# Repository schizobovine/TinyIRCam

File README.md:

# TinyIRCam
Simple mash up of a [TinyScreen+](https://tinycircuits.com/collections/all/products/tinyscreenplus) and a 8x8 [GridEye IR sensor breakout](https://www.tindie.com/products/onehorse/grid-eye-8-x-8-ir-array/>).

## Building
You will need the [TinyScreen+ board definition installed](https://tinycircuits.com/blogs/learn/158833543-tinyscreen-setup) in a working Arduino 1.6+ environment to build the code.

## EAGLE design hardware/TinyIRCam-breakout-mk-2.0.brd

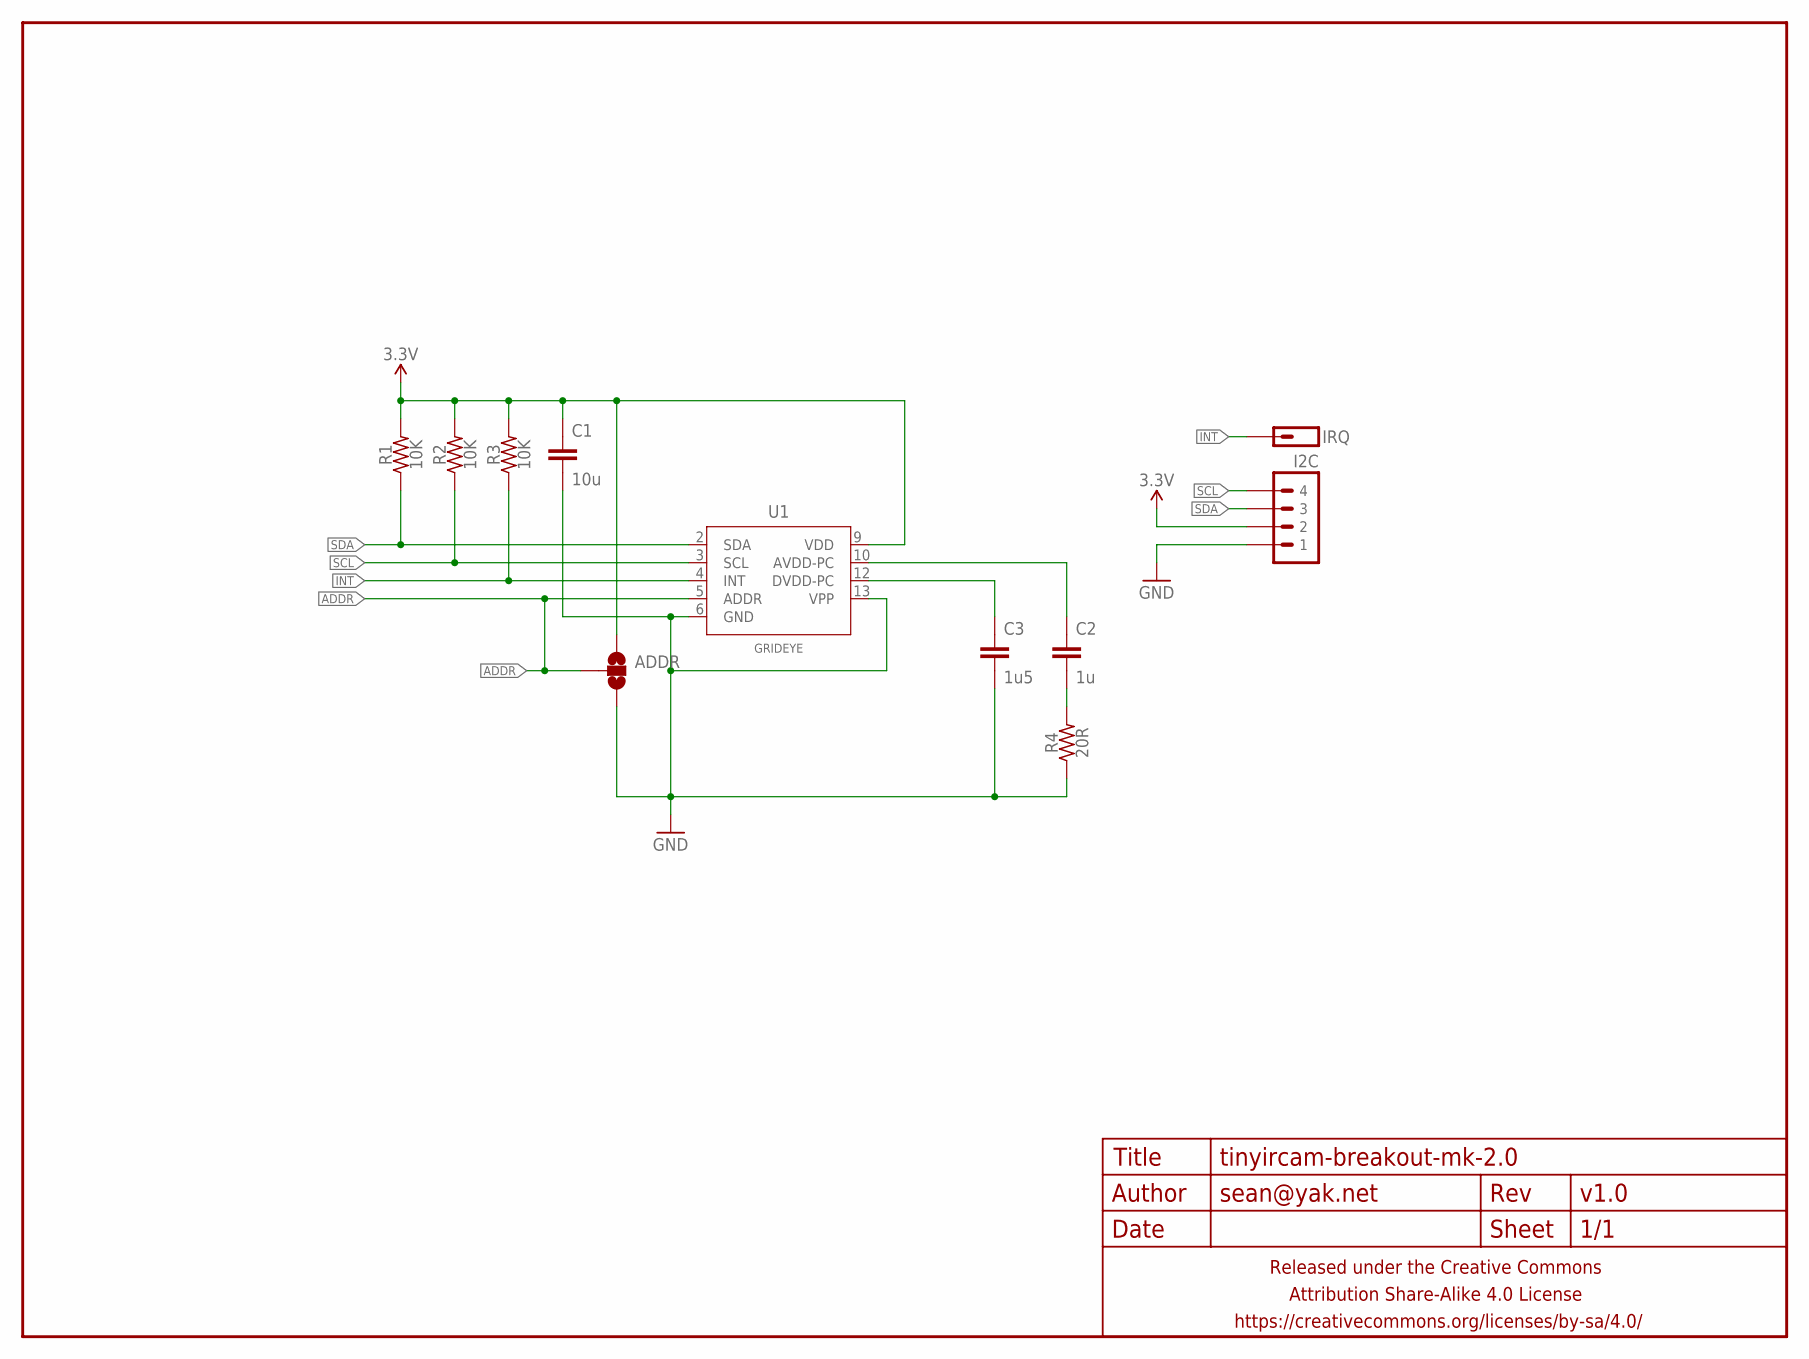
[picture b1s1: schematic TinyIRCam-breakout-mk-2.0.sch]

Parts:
ADDR: JUMPER-PAD-3-NOSMALLER; PAD-JUMPER-3-NO_YES_SILK_FULL_BOX_SMALLER
C1: 10u; C0603-TIGHTER
C2: 1u; C0603-TIGHTER
C3: 1u5; C0603-TIGHTER
FRAME1: FRAME-LETTERNO_PACKAGE; DUMMY
I2C: M04PTH-CENTERED; 1X04-PTH-VERT-CENTER
IRQ: M01PTH; 1X01
R1, R2, R3: 10K; R0603-TIGHTER
R4: 20R; R0603-TIGHTER
U1: GRIDEYE; GRIDEYE-FATTER

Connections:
3.3V: ADDR.1, C1.1, I2C.2, R1.2, R2.2, R3.2, U1.9 (VDD)
ADDR: ADDR.2, U1.5 (ADDR)
GND: ADDR.3, C1.2, C3.2, I2C.1, R4.1, U1.6 (GND), U1.13 (VPP)
INT: IRQ.1, R3.1, U1.4 (INT)
unnamed: C2.2, R4.2
unnamed: C3.1, U1.12 (DVDD-PC)
unnamed: C2.1, U1.10 (AVDD-PC)
SCL: I2C.4, R2.1, U1.3 (SCL)
SDA: I2C.3, R1.1, U1.2 (SDA)

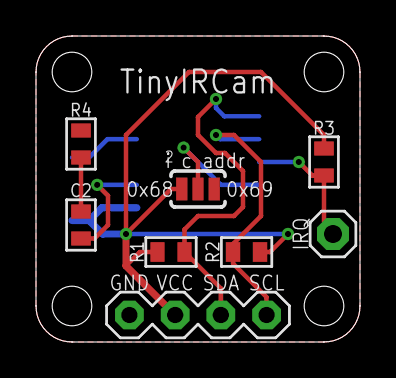
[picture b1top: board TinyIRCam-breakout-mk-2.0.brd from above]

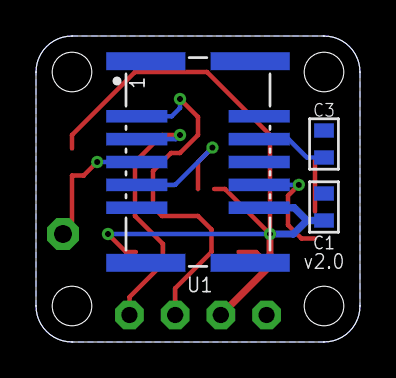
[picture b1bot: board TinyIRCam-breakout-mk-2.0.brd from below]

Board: 2 copper layers, 18.0 x 17.0 mm, 12 parts (3 on the bottom side), 9 nets.

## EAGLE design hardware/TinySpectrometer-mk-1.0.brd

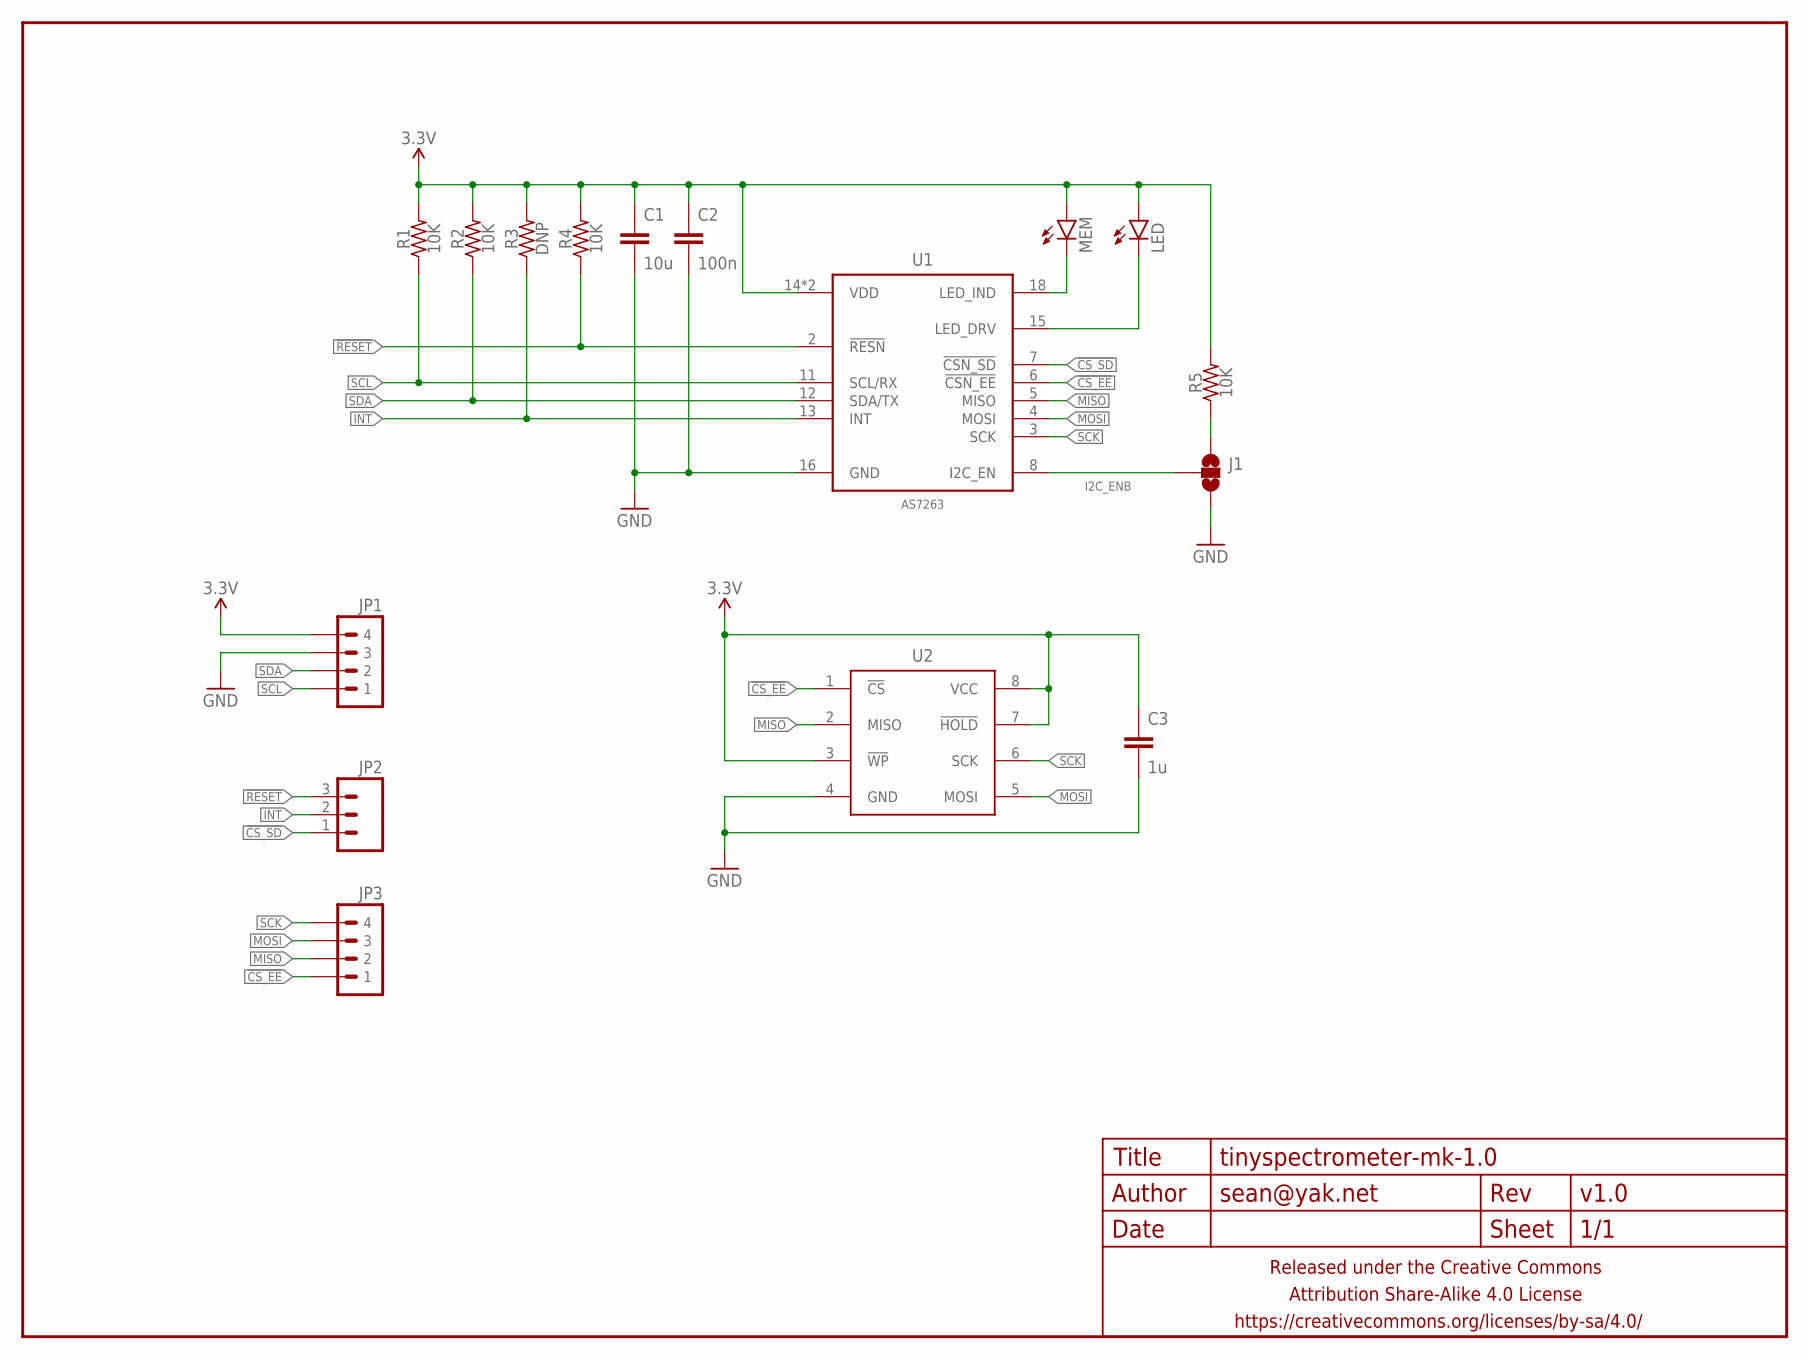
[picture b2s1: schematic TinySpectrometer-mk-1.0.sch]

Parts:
C1: 10u; C0603-TIGHTER
C2: 100n; C0603-TIGHTER
C3: 1u; C0603-TIGHTER
FRAME1: FRAME-LETTERNO_PACKAGE; DUMMY
J1: JUMPER-PAD-3-NOSMALLER; PAD-JUMPER-3-NO_YES_SILK_FULL_BOX_SMALLER
JP1, JP3: M04PTH-CENTERED; 1X04-PTH-VERT-CENTER
JP2: M03PTH-CENTERED; 1X03-CENTERED
LED: LED1206; LED-1206
MEM: LED0603-TIGHT; LED-0603-TIGHT
R1, R2, R4, R5: 10K; R0603-TIGHTER
R3: DNP; R0603-TIGHTER
U1: AS7263; AS7263-LGA20
U2: SPI_FLASHSOIC; SO08

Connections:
3.3V: C1.1, C2.1, C3.1, JP1.4, LED.A, MEM.A, R1.2, R2.2, R3.2, R4.2, R5.2, U1.14 (VDD), U1.17 (VDD), U2.3 (!WP), U2.7 (!HOLD), U2.8 (VCC)
!CS_EE: JP3.1, U1.6 (!CSN_EE), U2.1 (!CS)
!CS_SD: JP2.1, U1.7 (!CSN_SD)
!RESET: JP2.3, R4.1, U1.2 (!RESN)
GND: C1.2, C2.2, C3.2, J1.3, JP1.3, U1.16 (GND), U2.4 (GND)
I2C_ENB: J1.2, U1.8 (I2C_EN)
INT: JP2.2, R3.1, U1.13 (INT)
MISO: JP3.2, U1.5 (MISO), U2.2 (MISO)
MOSI: JP3.3, U1.4 (MOSI), U2.5 (MOSI)
unnamed: MEM.C, U1.18 (LED_IND)
unnamed: LED.C, U1.15 (LED_DRV)
unnamed: J1.1, R5.1
SCK: JP3.4, U1.3 (SCK), U2.6 (SCK)
SCL: JP1.1, R1.1, U1.11 (SCL/RX)
SDA: JP1.2, R2.1, U1.12 (SDA/TX)

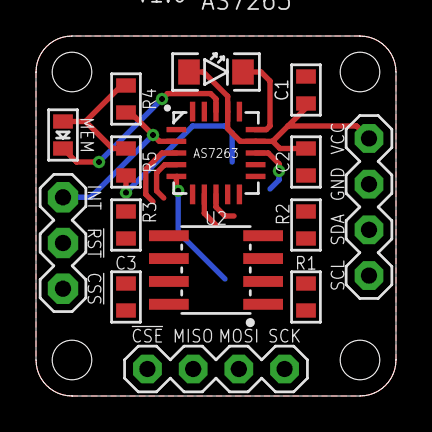
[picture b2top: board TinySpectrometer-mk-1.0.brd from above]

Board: 2 copper layers, 20.0 x 20.0 mm, 17 parts (1 on the bottom side), 15 nets.

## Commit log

2017-05-02 initial commit, display something on screen
2017-05-04 various tinkering before i found...
2017-05-04 removing in favor of already implemented lib
2017-05-04 working!
2017-05-04 it does stuff wooooo
2017-05-06 working until i fucked it all up
2017-05-06 welp have to make hardware for it which i probably won't fail at
2017-05-06 maybe i'll get around to making this board. maybe.
2017-07-03 adding gitignore
2017-07-03 whole lotta commits

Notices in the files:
parts and their libraries:
a_parts: Released under the Creative Commons Attribution Share-Alike 4.0 License
a_parts: https://creativecommons.org/licenses/by-sa/4.0
a_parts: Released under the Creative Commons
